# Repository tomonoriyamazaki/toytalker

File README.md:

# ToyTalker

子供向け音声AIおもちゃ。話しかけると、好きなキャラクターの声で返事をしてくれる。

## 特徴

- **応答約2秒**: STT→LLM→TTSを全区間ストリーミングでつなぎ、最初の音声チャンクが生成され次第再生を開始。サーバーレス（AWS Lambda）構成のまま体感レイテンシを最小化
- **相槌**: メインの応答を生成している間に「そうだね〜」などの短い繋ぎ応答を先に返し、会話のテンポを保つ
- **ボイス・キャラクター切替**: TTSプロバイダーをプラガブルに切替可能（OpenAI / Google / Gemini / ElevenLabs / Cartesia / FishAudio / ずんだもん / 自前クローンボイス）。キャラクターの人格プロンプトもDBで管理
- **スタンドアロン動作**: ESP32-S3搭載の専用基板、おもちゃ単体でWiFi経由でAWSと直接通信（設定ではスマホが必要）

## しくみ
https://github.com/user-attachments/assets/177e0598-6c0a-4d14-9477-36d719003d13

```
[スマホアプリ / ESP32] ── 音声 ──> Soniox STT（直接WebSocket接続）
        │                              │ テキスト
        │                              v
        │<── 音声ストリーム ── Lambda（LLM → TTS ストリーミング）
        │<── 繋ぎ応答 ─────── Lambda（相槌）
```

- STTはLambdaを経由せず、一時キーを使ってクライアントからSonioxへ直接接続（ボトルネック回避）
- LLM→TTSは直列ストリーミングで、生成しながら順次音声化・再生

## デバイスの変遷

| 世代 | 構成 | 状態 |
|---|---|---|
| v1 | Raspberry Pi | 検証完了 |
| v2 | ブレッドボード | 検証完了 |
| v3 | ESP32-S3スタンドアロン（専用PCB） | 開発中 |

## 参加プログラム

- SS Bootcamp 3rd #2025
- TiB FAB makers challenge 2025
- SS Bootcamp 4th #2026

## ドキュメント

- [開発のあゆみ（初期からの検討・試行錯誤の記録）](docs/history.md)
- [マイコン（ESP32）実装](docs/mcu.md)
- [スマホアプリ実装](app/README.md)
- [自前クローンボイス（RTX 5090 / Qwen3-TTS）のバッチ推論](docs/qwen3-tts-batch-engine-2026-09-12.md)
- [原価と課金の考え方](docs/pricing-and-cost-model.md)
- [製品化の認証チェックリスト（STマーク・技適・PSE）](docs/certification-checklist.md)

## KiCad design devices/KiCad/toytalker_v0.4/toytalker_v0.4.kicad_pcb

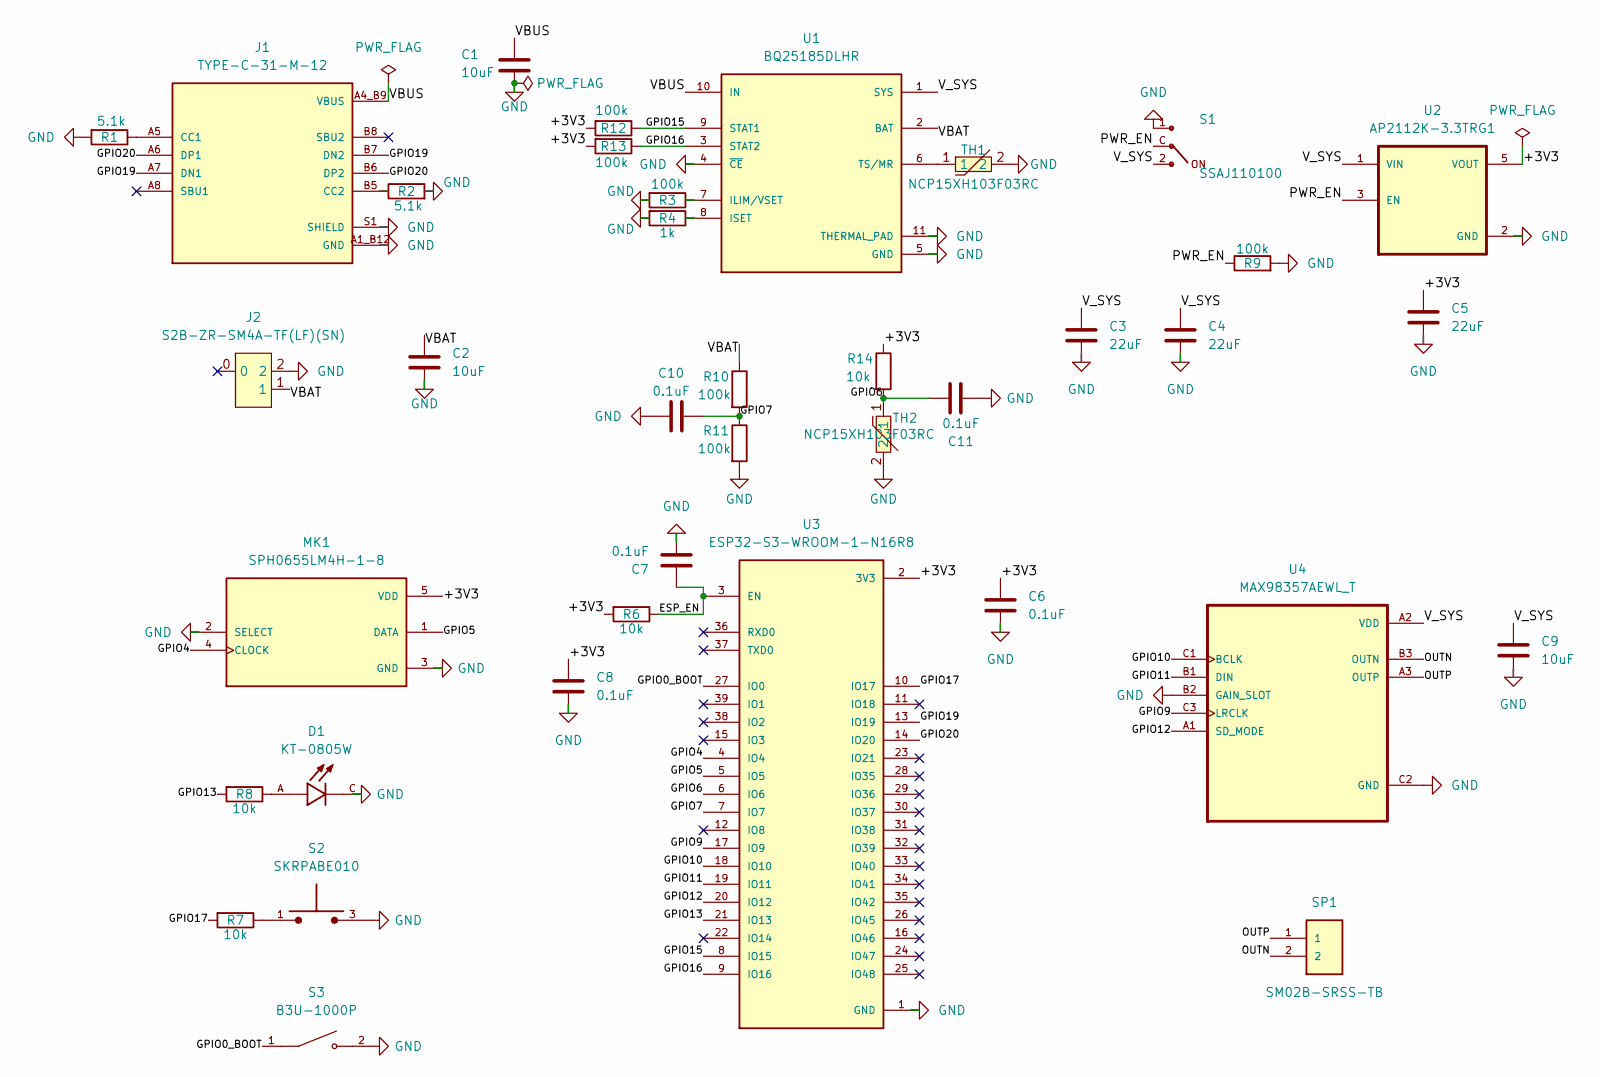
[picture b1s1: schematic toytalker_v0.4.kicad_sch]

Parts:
C1, C2, C9: 10uF; C_0603_1608Metric; LCSC Part C19702
C3, C4, C5: 22uF; C_0603_1608Metric; LCSC Part C59461
C6, C7, C8, C10, C11: 0.1uF; C_0402_1005Metric; LCSC Part C1525
D1: KT-0805W; LED_KT-0805W; PARTREV 2017.05.16; LCSC Part C34499
J1: TYPE-C-31-M-12; HRO_TYPE-C-31-M-12; PARTREV 2020.12.08; LCSC Part C165948
J2: S2B-ZR-SM4A-TF(LF)(SN); CONN-SMD_S2B-ZR-SM4A; LCSC Part C265329
MK1: SPH0655LM4H-1-8; MIC_SPH0655LM4H-1; LCSC Part C22376158
R1, R2: 5.1k; R_0402_1005Metric; LCSC Part C25905
R3, R9, R10, R11, R12, R13: 100k; R_0402_1005Metric; LCSC Part C25741
R4: 1k; R_0402_1005Metric; LCSC Part C11702
R6, R7, R8, R14: 10k; R_0402_1005Metric; LCSC Part C25744
S1: SSAJ110100; SW_SSAJ110100; LCSC Part C160863
S2: SKRPABE010; SW_SKRPABE010; LCSC Part C115360
S3: B3U-1000P; SW_B3U-1000P; LCSC Part C231329
SP1: SM02B-SRSS-TB; SM02B-SRSS-TB_LF__SN_; LCSC Part C160402
TH1, TH2: NCP15XH103F03RC; R0402; LCSC Part C77131
U1: BQ25185DLHR; IC_BQ25185DLHR; PARTREV OCTOBER 2023; LCSC Part C19725033
U2: AP2112K-3.3TRG1; SOT95P285X140-5N; PARTREV 2-2; LCSC Part C23380830
U3: ESP32-S3-WROOM-1-N16R8; XCVR_ESP32S3WROOM1N8R8; LCSC Part C2913202
U4: MAX98357AEWL_T; BGA9N40P3X3_134X143X69N; LCSC Part C2682619

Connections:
/+3V3: C5.1, C6.1, C8.1, MK1.5 (VDD), R6.2, R12.2, R13.2, R14.1, U2.5 (VOUT), U3.2 (3V3)
/ESP_EN: C7.1, R6.1, U3.3 (EN)
/GPIO0_BOOT: S3.1, U3.27 (IO0)
/GPIO4: MK1.4 (CLOCK), U3.4 (IO4)
/GPIO5: MK1.1 (DATA), U3.5 (IO5)
/GPIO6: C11.1, R14.2, TH2.1, U3.6 (IO6)
/GPIO7: C10.1, R10.2, R11.1, U3.7 (IO7)
/GPIO9: U3.17 (IO9), U4.C3 (LRCLK)
/GPIO10: U3.18 (IO10), U4.C1 (BCLK)
/GPIO11: U3.19 (IO11), U4.B1 (DIN)
/GPIO12: U3.20 (IO12), U4.A1 (SD_MODE)
/GPIO13: R8.2, U3.21 (IO13)
/GPIO15: R12.1, U1.9 (STAT1), U3.8 (IO15)
/GPIO16: R13.1, U1.3 (STAT2), U3.9 (IO16)
/GPIO17: R7.2, U3.10 (IO17)
/GPIO19: J1.A7 (DN1), J1.B7 (DN2), U3.13 (IO19)
/GPIO20: J1.A6 (DP1), J1.B6 (DP2), U3.14 (IO20)
/OUTN: SP1.2, U4.B3 (OUTN)
/OUTP: SP1.1, U4.A3 (OUTP)
/PWR_EN: R9.1, S1.C, U2.3 (EN)
/VBAT: C2.1, J2.1, R10.1, U1.2 (BAT)
/V_SYS: C3.1, C4.1, C9.1, S1.2, U1.1 (SYS), U2.1 (VIN), U4.A2 (VDD)
GND: C1.2, C2.2, C3.2, C4.2, C5.2, C6.2, C7.2, C8.2, C9.2, C10.2, C11.2, D1.C, J1.A1_B12 (GND), J1.B1_A12 (GND), J1.S1 (SHIELD), J1.S2 (SHIELD), J1.S3 (SHIELD), J1.S4 (SHIELD), J2.2, MK1.2 (SELECT), MK1.3 (GND), R1.2, R2.2, R3.2, R4.2, R9.2, R11.2, S1.1, S2.3, S2.4, S3.2, TH1.2, TH2.2, U1.4 (~CE), U1.5 (GND), U1.11 (THERMAL_PAD), U1.12 (THERMAL_PAD), U1.13 (THERMAL_PAD), U2.2 (GND), U3.1 (GND), U3.40 (GND), U3.41_1 (GND), U3.41_2 (GND), U3.41_3 (GND), U3.41_4 (GND), U3.41_5 (GND), U3.41_6 (GND), U3.41_7 (GND), U3.41_8 (GND), U3.41_9 (GND), U3.41_10 (GND), U3.41_11 (GND), U3.41_12 (GND), U3.41_13 (GND), U3.41_14 (GND), U3.41_15 (GND), U3.41_16 (GND), U3.41_17 (GND), U3.41_18 (GND), U3.41_19 (GND), U3.41_20 (GND), U3.41_21 (GND), U4.B2 (GAIN_SLOT), U4.C2 (GND)
unnamed: D1.A, R8.1
unnamed: J1.A5 (CC1), R1.1
unnamed: J1.B5 (CC2), R2.1
unnamed: R7.1, S2.1, S2.2
unnamed: R3.1, U1.7 (ILIM/VSET)
unnamed: R4.1, U1.8 (ISET)
unnamed: TH1.1, U1.6 (TS/MR)
VBUS: C1.1, J1.A4_B9 (VBUS), J1.B4_A9 (VBUS), U1.10 (IN)

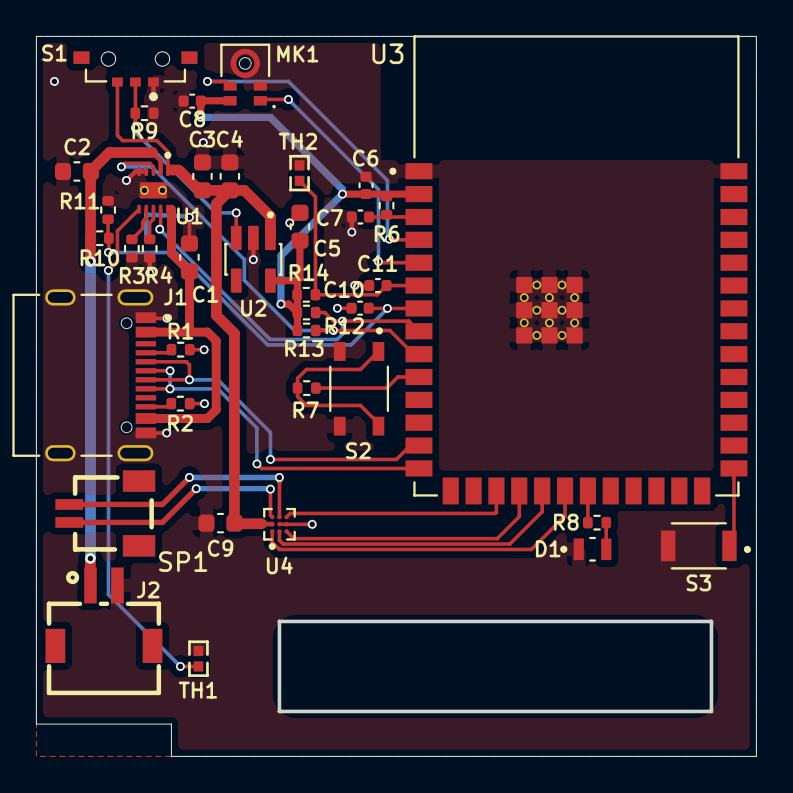
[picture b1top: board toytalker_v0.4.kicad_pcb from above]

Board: 2 copper layers, 40.0 x 40.0 mm, 38 parts (0 on the bottom side), 31 nets.

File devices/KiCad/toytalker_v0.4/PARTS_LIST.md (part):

# v0.4 パーツ一覧（ESP32-S3-WROOM-1-N16R8。2026-11-22）

> **このファイルの役割: 「今の正」。** 部品の値・ネット・役割の唯一の基準。BOM作成・発注チェック・値の確認はこのファイルだけを見る。変更したら必ずここを更新する。
> 変更の理由 → [マイコン](../../../docs/mcu.md) の「v0.4 で変えること」/ GPIO → [PINMAP.md](PINMAP.md) / v0.3 までの経緯 → [v0.3 の PARTS_LIST.md](../toytalker_mini_v0.3/PARTS_LIST.md) と [v0.2 の PARTS_AND_POWER.md](../toytalker_mini_v0.2/PARTS_AND_POWER.md)

検証方法: `toytalker_v0.4.kicad_sch` から全部品の値・フットプリント・`LCSC Part` を取り出し、ネットリスト（`kicad-cli sch export netlist`）で接続先を照合した。ERC 0件。部品は 38 個・20 種類。

## v0.3 からの変更点

| Ref | v0.3 | v0.4 | 理由・注意 |
|---|---|---|---|
| **U3** | ESP32-S3-MINI-1-N4R2 | **ESP32-S3-WROOM-1-N16R8**（C2913202） | フラッシュ 16MB・PSRAM 8MB（8 線）。18.0×25.5×3.1mm、縦置きでアンテナは基板の上辺。GPIO35〜37 は PSRAM が使うので配線しない。ビルドは `PSRAM=opi`・`FlashSize=16M`（MINI 機と同じ .bin は動かない） |
| **SP1** | HC-1.25-2PWT（MX1.25） | **SM02B-SRSS-TB**（JST SH 2P、C160402） | 小さくするため。差し口は基板の内側向き。1 = OUTP、2 = OUTN。固定用のパッド 3・4 はどこにもつながない |
| **R3** | 13kΩ（充電電圧 4.2V） | **100kΩ**（**4.1V**） | USB を挿したままでの電池の劣化を抑える。入力の上限は 1100mA のまま（BQ25185 データシート表 6-1）。使える容量は 1 割ほど減る見込み |
| **R4** | 620Ω（充電 484mA） | **1kΩ**（**300mA**） | 充電中の発熱と電池への負担を減らす（充電電流 = 300 / R）。充電時間は約 1.6 倍 |
| **R8** | 1.5kΩ | **10kΩ** | LED をさらに暗く（約 0.05〜0.07mA）。v0.3 の試験機で PWM 15% 相当に決めた |
| **R10・R11** | 470kΩ ×2 | **100kΩ ×2** | 電池の分圧。比は 1/2 のままで、計算式は変わらない。常時の電流は約 4.5 → 21µA |
| **C10・C11** | 0603 | **0402** | 0.1µF を 0402 に統一 |
| **U4** の GAIN | 未接続（9dB） | **GND**（12dB） | 隣の玉（C2 = GND）へ直結。効くかは実機で確認 |
| **U1** のシンボル | ピン 11 まで | **放熱ビア 12・13 を足した** | 基板の放熱ビア 2 個が「回路図から基板を更新」で GND から外れないように |
| ピン割当 | - | 全面的に変更 | [PINMAP.md](PINMAP.md)。アンプの BCLK と WS は配線の都合で入れ替えた（GPIO9 = WS、GPIO10 = BCLK） |

## パーツ一覧 ※電気の流れ順

### USB受電 → 充電IC
| Ref | 値 | ネット | 役割 |
|---|---|---|---|
| J1 | TYPE-C-31-M-12 | VBUS、GPIO19（D−）・GPIO20（D+） | USB-C。電源入力と USB-Serial/JTAG |
| R1 | 5.1kΩ | CC1 | USB-C「5V/3Aください」の名札(必須) |
| R2 | 5.1kΩ | CC2 | 同上(ケーブル裏表対応) |
| C1 | 10uF | VBUS | BQ25185のIN入力デカップリング |
| U1 | BQ25185 | - | 電源制御。充電しながら電力供給(パワーパス)。STAT1 → GPIO15、STAT2 → GPIO16 |
| R3 | **100kΩ** | ILIM/VSET | 🔁 充電電圧 4.1V・USB から最大 1.1A 受電の設定 |
| R4 | **1kΩ** | ISET | 🔁 バッテリーへ 300mA 充電の設定 |
| TH1 | NCP15XH103F03RC | TS/MR | 充電温度保護サーミスタ。高温/低温でBQが充電を自動停止。**電池コネクタの横に置く**（充電 IC のそばだと IC の熱を拾う） |

### バッテリー
| Ref | 値 | ネット | 役割 |
|---|---|---|---|
| J2 | S2B-ZR-SM4A-TF | VBAT | バッテリーコネクタ(JST ZH、φ1.0被覆線対応) |
| C2 | 10uF | VBAT | BQ25185のBAT側デカップリング |

### システム電源 V_SYS（常時通電）
| Ref | 値 | ネット | 役割 |
|---|---|---|---|
| C3 | 22uF | V_SYS | BQ25185のSYS出力デカップリング |
| C4 | 22uF | V_SYS | 同上追加分 |

### 電源スイッチ（EN方式 = 信号だけを切り替える）
| Ref | 値 | ネット | 役割 |
|---|---|---|---|
| S1 | SSAJ110100 | PWR_EN | スライドスイッチ（ALPS、横操作、SPDT）。C→PWR_EN、2→V_SYS、1→GND。C–2 が閉じると ON（大電流は流れない） |
| R9 | 100kΩ | PWR_EN | プルダウン。スイッチ切替中にENが宙ぶらりんになるのを防ぐ「重り」 |

### LDO → +3V3
| Ref | 値 | ネット | 役割 |
|---|---|---|---|
| U2 | AP2112K-3.3 | - | LDO。V_SYS→3.3Vに降圧。ENピンがPWR_ENで電源ON/OFF |
| C5 | 22uF | +3V3 | LDO出力デカップリング |
| C6 | 0.1uF | +3V3 | ESP32直近の高周波デカップリング（2 番ピンの横） |
| C8 | 0.1uF | +3V3 | マイク直近デカップリング（マイクの 3V3 のパッドの横。マイクを動かしたら一緒に動かす） |

### ESP32まわり
| Ref | 値 | ネット | 役割 |
|---|---|---|---|
| U3 | **ESP32-S3-WROOM-1-N16R8** | - | 🔁 本体（18.0×25.5mm、アンテナ部 6mm を含む） |
| R6 | 10kΩ | ESP_EN | ENプルアップ |
| C7 | 0.1uF | ESP_EN | ENの立ち上がり遅延+ノイズフィルタ |
| S3 | B3U-1000P | GPIO0_BOOT | Bootボタン |
| S2 | SKRPABE010 | GPIO17（R7 経由） | 機能ボタン(押すとGND) |
| R7 | 10kΩ | GPIO17 | ボタンとGPIOの間の直列抵抗(ピン保護) ※プルダウンではない |
| D1 | KT-0805W | GPIO13（R8 経由） | 単色LED（白、Vf 2.6〜3.0V @2mA、IF max 20mA） |
| R8 | **10kΩ** | GPIO13 | 🔁 LED電流制限（約 0.05〜0.07mA） |

### 監視・計測
| Ref | 値 | ネット | 役割 |
|---|---|---|---|
| R10 | **100kΩ** | VBAT→GPIO7 | 🔁 電池残量分圧の上側 |
| R11 | **100kΩ** | GPIO7→GND | 🔁 電池残量分圧の下側 |
| C10 | 0.1uF | GPIO7 | ADC安定化(WiFiノイズ平滑) |
| R12 | 100kΩ | GPIO15 | 充電状態STAT1プルアップ(STATはオープンドレインのため必須) |
| R13 | 100kΩ | GPIO16 | 充電状態STAT2プルアップ |
| R14 | 10kΩ | +3V3→GPIO6 | 基板温度分圧の上側 |
| TH2 | NCP15XH103F03RC | GPIO6→GND | 基板温度サーミスタ(分圧の下側) |
| C11 | 0.1uF | GPIO6 | ADC安定化 |

### 音声
| Ref | 値 | ネット | 役割 |
|---|---|---|---|
| MK1 | SPH0655LM4H-1-8 | GPIO4(CLOCK)/GPIO5(DATA) | **PDM** マイク。1=DATA→GPIO5、2=SELECT→GND、3=GND(リング)、4=CLOCK→GPIO4、5=VDD→+3V3。基板の上辺（電源スイッチの右隣）。音は基板の穴（Ø0.65）を通って裏側から入る |
| U4 | MAX98357A | - | I2Sアンプ。VDDは**V_SYS直結**。BCLK=GPIO10、LRCLK(WS)=GPIO9、DIN=GPIO11、SD=GPIO12、**GAIN=GND（12dB）** |
| C9 | 10uF | **V_SYS** | アンプVDDデカップリング ※+3V3ではない |
| SP1 | **SM02B-SRSS-TB** | OUTP/OUTN | 🔁 スピーカーコネクタ(JST SH) |

## プレフィックス順サマリ
- **J**: J1 USB-C / J2 バッテリー(ZH)
- **U**: U1 BQ25185 / U2 AP2112K / U3 ESP32-S3-WROOM-1-N16R8 / U4 MAX98357A
- **S**: S1 電源スライド(SSAJ110100) / S2 機能 / S3 Boot
- **R**: R1,R2=5.1k(CC) **R3=100k(ILIM/VSET)** **R4=1k(ISET)** R6=10k(EN) R7=10k(ボタン直列) **R8=10k(LED)** R9=100k(PWR_ENプルダウン) **R10,R11=100k(残量分圧)** R12,R13=100k(STATプルアップ) R14=10k(温度分圧)（R5 は欠番）
- **C**: C1,C2=10u(VBUS/VBAT) C3,C4=22u(V_SYS) C5=22u,C6=0.1u,C8=0.1u(+3V3) C7=0.1u(EN) C9=10u(V_SYS アンプ) C10,C11=0.1u(ADC)
- **TH**: TH1 充電保護 / TH2 基板温度 (同一品NCP15XH103F03RC)
- **他**: D1 LED / MK1 マイク(PDM) / SP1 スピーカー(SH)

## 発注用の一覧（LCSC 番号と Basic / Extended）

JLCPCB の部品データの写し（jlcsearch.tscircuit.com）で 2026-11-22 に引いた。**20 種類のうち Basic 8・Extended 12**（v0.3 は 23 種類のうち Extended 15）。在庫と Basic かどうかは発注前に注文画面で見直す。

| LCSC | 部品 | サイズ | Ref | 個数 | 区分 |
|---|---|---|---|---|---|
| C1525 | 0.1µF | 0402 | C6 C7 C8 C10 C11 | 5 | Basic |
| C19702 | 10µF | 0603 | C1 C2 C9 | 3 | Basic |
| C59461 | 22µF | 0603 | C3 C4 C5 | 3 | Basic |
| C25905 | 5.1kΩ | 0402 | R1 R2 | 2 | Basic |
| C11702 | 1kΩ | 0402 | R4 | 1 | Basic |
| C25744 | 10kΩ | 0402 | R6 R7 R8 R14 | 4 | Basic |
| C25741 | 100kΩ | 0402 | R3 R9 R10 R11 R12 R13 | 6 | Basic |
| C34499 | KT-0805W（白 LED） | 0805 | D1 | 1 | Basic |
| C77131 | NCP15XH103F03RC（サーミスタ 10kΩ） | 0402 | TH1 TH2 | 2 | Extended |
| C165948 | TYPE-C-31-M-12 | - | J1 | 1 | Extended |
| C265329 | S2B-ZR-SM4A-TF(LF)(SN) | - | J2 | 1 | Extended |
| C160402 | SM02B-SRSS-TB(LF)(SN) | - | SP1 | 1 | Extended |
| C22376158 | SPH0655LM4H-1-8 | - | MK1 | 1 | Extended |
| C160863 | SSAJ110100 | - | S1 | 1 | Extended |
| C115360 | SKRPABE010 | - | S2 | 1 | Extended |
| C231329 | B3U-1000P | - | S3 | 1 | Extended |
| C19725033 | BQ25185DLHR | - | U1 | 1 | Extended |
| C23380830 | AP2112K-3.3TRG1 | SOT-23-5 | U2 | 1 | Extended |
| C2913202 | ESP32-S3-WROOM-1-N16R8 | - | U3 | 1 | Extended |
| C2682619 | MAX98357AEWL+T | WLP-9 | U4 | 1 | Extended |

Extended のまま残した理由（LDO・サーミスタは Basic に合う品が無い）は [マイコン](../../../docs/mcu.md) の「v0.4 で変えること」14。

## JLCPCB の位置補正（Fabrication Toolkit 用）

`python devices/KiCad/tools/jlc_offset_check.py devices/KiCad/toytalker_v0.4/toytalker_v0.4.kicad_pcb` で照合した（2026-11-22）。値は回路図の部品の欄が正本で、基板のフットプリントへも写してある（道具の「今の値と違う」は 0 件）。

| Ref | FT Position Offset | FT Rotation Offset | メモ |
|---|---|---|---|
| J1 | 0,2.324 | - | v0.3 と同じ |
| MK1 | 0,0.706 | - | v0.3 と同じ |
| S1 | 0,0.603 | - | v0.3 と同じ |
| **SP1** | **0,0.038** | - | 新規。0.04mm なので実質ゼロ。向きは 0° で一致（固定用のパッド 3・4 の番号だけ JLC 側と左右が逆で、どちらも未接続なので問題ない） |
| **U3** | **0,-3.627** | - | 新規。JLC 側の原点はピンの並びの中心、うちはモジュール本体の中心で、その差。1〜40 番ピンで重ねて誤差 0.02mm |
| U1 | - | 270 | v0.3 と同じ |
| U2 | - | 180 | v0.3 と同じ |
| U4 | - | 180 | v0.3 と同じ |

D1（LED）はパッドの名前が JLC 側と違い（A/C と 1/2）、道具では向きを決められない。v0.3 と同じ部品・同じフットプリントで、v0.3 の注文で向きが合っていた。

## パッケージサイズの使い分け

サイズ表記: **0402** = 1.0×0.5mm / **0603** = 1.6×0.8mm（インチ由来の呼び名。メートル表記だと1005/1608でKiCadのフットプリント名はこちら）

| 種類 | サイズ | 理由 |
|---|---|---|
| 抵抗 全部(R1〜R14, TH1/TH2) | **0402** | 抵抗のサイズは**発熱**で決まり、値は無関係 |
| コンデンサ 0.1µF (C6/C7/C8/C10/C11) | **0402** | 小容量は小さい体積で作れる |
| コンデンサ 10〜22µF (C1〜C5, C9) | **0603** | 容量は物理体積が必要。0402の10µFは高価な上、電圧がかかると実効容量が大きく落ちる(DCバイアス特性)ため0603が定石 |

## 設計の状態（2026-11-22）

- **未発注（製造ファイルまで済み）。** 回路図・配置・配線・スピーカーの裏のくり抜き・アンテナのキープアウトまで済み。経過と残りは [マイコン](../../../docs/mcu.md) の「v0.4 の状態」。
- **ERC**: 0件。**DRC**（ゾーン再充填後、回路図との照合つき）: 未配線 0、間隔の違反なし。残る指摘は既知のもの（U4 BGA のマスク橋渡し 12、J1 シールドの基板端 0.48mm 2、U3・J1 の外形線が基板端にかかる 5、シルクの重なり、U3 の 40 番ピンのベタとのつながりが細い 1）。
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
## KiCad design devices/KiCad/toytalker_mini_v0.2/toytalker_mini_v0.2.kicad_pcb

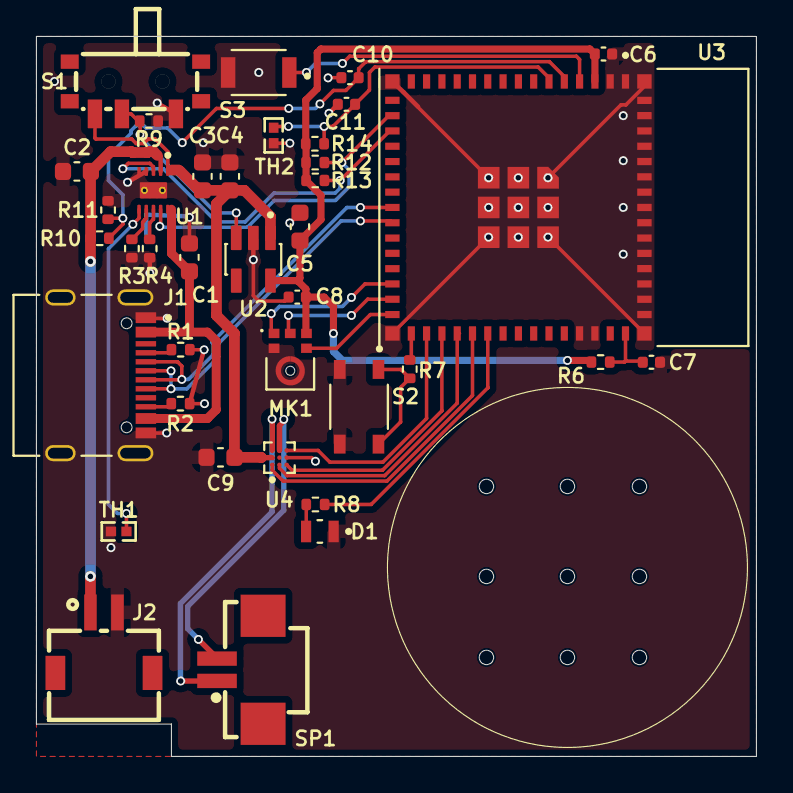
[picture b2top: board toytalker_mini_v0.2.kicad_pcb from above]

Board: 2 copper layers, 40.0 x 40.0 mm, 38 parts (0 on the bottom side), 32 nets.

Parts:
C1, C2, C9: 10uF; C_0603_1608Metric
C3, C4, C5: 22uF; C_0603_1608Metric
C6, C7, C8, C10, C11: 0.1uF; C_0402_1005Metric
D1: KT-0805W; LED_KT-0805W
J1: TYPE-C-31-M-12; HRO_TYPE-C-31-M-12
J2: S2B-ZR-SM4A-TF(LF)(SN); CONN-SMD_S2B-ZR-SM4A
MK1: SPH0645LM4H-1-8; MIC_SPH0645LM4H-B
R1, R2: 5.1k; R_0402_1005Metric
R3: 13k; R_0402_1005Metric
R4: 620; R_0402_1005Metric
R6, R7, R14: 10k; R_0402_1005Metric
R8: 470; R_0402_1005Metric
R9, R12, R13: 100k; R_0402_1005Metric
R10, R11: 470k; R_0402_1005Metric
S1: MSK12C02G15-B; SW-SMD_MSK12C02G15-B
S2: SKRPABE010; SW_SKRPABE010
S3: B3U-1000P; SW_B3U-1000P
SP1: HC-1.25-2PWT; CONN-SMD_2P-P1.25-HC-1.25-2PWT
TH1, TH2: NCP15XH103F03RC; R0402
U1: BQ25185DLHR; IC_BQ25185DLHR
U2: AP2112K-3.3TRG1; SOT95P285X140-5N
U3: ESP32-S3-MINI-1-N4R2; XCVR_ESP32-S3-MINI-1-N4R2
U4: MAX98357AEWL_T; BGA9N40P3X3_134X143X69N

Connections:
/+3V3: C5.1, C6.1, C8.1, MK1.5 (VDD), R6.2, R12.2, R13.2, R14.1, U2.5 (VOUT), U3.3 (3V3)
/ESP_EN: C7.1, R6.1, U3.45 (EN)
/GPIO0_BOOT: S3.1, U3.4 (IO0)
/GPIO1: C10.1, R10.2, R11.1, U3.5 (IO1)
/GPIO2: C11.1, R14.2, TH2.1, U3.6 (IO2)
/GPIO13: R12.1, U1.9 (STAT1), U3.17 (IO13)
/GPIO14: R13.1, U1.3 (STAT2), U3.18 (IO14)
/GPIO19: J1.A7 (DN1), J1.B7 (DN2), U3.23 (IO19)
/GPIO20: J1.A6 (DP1), J1.B6 (DP2), U3.24 (IO20)
/GPIO33: MK1.1 (WS), U3.28 (IO33)
/GPIO34: MK1.6 (DATA_OUT), U3.29 (IO34)
/GPIO35: R7.2, U3.31 (IO35)
/GPIO36: U3.32 (IO36), U4.C3 (LRCLK)
/GPIO37: U3.33 (IO37), U4.C1 (BCLK)
/GPIO38: U3.34 (IO38), U4.B1 (DIN)
/GPIO39: U3.35 (IO39), U4.A1 (SD_MODE)
/GPIO40: R8.2, U3.36 (IO40)
/GPIO48: MK1.4 (BCLK), U3.30 (IO48)
/OUTN: SP1.2, U4.B3 (OUTN)
/OUTP: SP1.1, U4.A3 (OUTP)
/PWR_EN: R9.1, S1.2, U2.3 (EN)
/VBAT: C2.1, J2.1, R10.1, U1.2 (BAT)
/V_SYS: C3.1, C4.1, C9.1, S1.1, U1.1 (SYS), U2.1 (VIN), U4.A2 (VDD)
GND: C1.2, C2.2, C3.2, C4.2, C5.2, C6.2, C7.2, C8.2, C9.2, C10.2, C11.2, D1.C, J1.A1_B12 (GND), J1.B1_A12 (GND), J1.S1 (SHIELD), J1.S2 (SHIELD), J1.S3 (SHIELD), J1.S4 (SHIELD), J2.2, MK1.2 (SELECT), MK1.3 (GND), R1.2, R2.2, R3.2, R4.2, R9.2, R11.2, S1.3, S2.3, S2.4, S3.2, TH1.2, TH2.2, U1.4 (~CE), U1.5 (GND), U1.11 (THERMAL_PAD), U1.12, U1.13, U2.2 (GND), U3.1 (GND), U3.2 (GND), U3.42 (GND), U3.43 (GND), U3.46 (GND), U3.47 (GND), U3.48 (GND), U3.49 (GND), U3.50 (GND), U3.51 (GND), U3.52 (GND), U3.53 (GND), U3.54 (GND), U3.55 (GND), U3.56 (GND), U3.57 (GND), U3.58 (GND), U3.59 (GND), U3.60 (GND), U3.61 (GND), U3.61_1 (GND), U3.61_2 (GND), U3.61_3 (GND), U3.61_4 (GND), U3.61_5 (GND), U3.61_6 (GND), U3.61_7 (GND), U3.61_8 (GND), U3.62 (GND), U3.63 (GND), U3.64 (GND), U3.65 (GND), U4.C2 (GND)
unnamed: D1.A, R8.1
unnamed: J1.A5 (CC1), R1.1
unnamed: J1.B5 (CC2), R2.1
unnamed: R7.1, S2.1, S2.2
unnamed: R3.1, U1.7 (ILIM/VSET)
unnamed: R4.1, U1.8 (ISET)
unnamed: TH1.1, U1.6 (TS/MR)
VBUS: C1.1, J1.A4_B9 (VBUS), J1.B4_A9 (VBUS), U1.10 (IN)

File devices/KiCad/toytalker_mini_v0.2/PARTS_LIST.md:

# v0.2 パーツ一覧（回路図から機械抽出した実値・2026-08-29検証）

> **このファイルの役割: 「今の正」。** 部品の値・ネット・役割の唯一の基準。BOM作成・発注チェック・値の確認はこのファイルだけを見る。変更したら必ずここを更新する。
> 経緯・理由 → PARTS_AND_POWER.md / 作業ログ → SCHEMATIC_CHECKLIST.md / GPIO → PINMAP.md

検証方法: `toytalker_mini_v0.2.kicad_sch` から全Reference/Valueを抽出し、ネットリストで接続先を照合。

## パーツ一覧 ※電気の流れ順

### USB受電 → 充電IC
| Ref | 値 | ネット | 役割 |
|---|---|---|---|
| J1 | TYPE-C-31-M-12 | VBUS | USB-C電源入力 |
| R1 | 5.1kΩ | CC1 | USB-C「5V/3Aください」の名札(必須) |
| R2 | 5.1kΩ | CC2 | 同上(ケーブル裏表対応) |
| C1 | 10uF | VBUS | BQ25185のIN入力デカップリング |
| U1 | BQ25185 | - | 電源制御。充電しながら電力供給(パワーパス) |
| R3 | 13kΩ | ILIM/VSET | USBから最大1.1A受電の設定 |
| R4 | **620Ω** | ISET | バッテリーへ500mA充電の設定 |
| TH1 | NCP15XH103F03RC | TS/MR | 🆕 充電温度保護サーミスタ。高温/低温でBQが充電を自動停止(旧R5の置き換え) |

### バッテリー
| Ref | 値 | ネット | 役割 |
|---|---|---|---|
| J2 | S2B-ZR-SM4A-TF | VBAT | 🆕 バッテリーコネクタ(JST ZH。旧SHから変更、φ1.0被覆線対応) |
| C2 | 10uF | VBAT | BQ25185のBAT側デカップリング |

### システム電源 V_SYS（常時通電）
| Ref | 値 | ネット | 役割 |
|---|---|---|---|
| C3 | 22uF | V_SYS | BQ25185のSYS出力デカップリング |
| C4 | 22uF | V_SYS | 同上追加分 ※旧V_SYS_SW用→v0.2でV_SYS_SW系統は廃止 |

### 電源スイッチ（EN方式 = 信号だけを切り替える）
| Ref | 値 | ネット | 役割 |
|---|---|---|---|
| S1 | MSK12C02G15-B | PWR_EN | 🆕 スライドスイッチ。V_SYS/GNDを選んでPWR_ENへ(大電流は流れない) |
| R9 | 100kΩ | PWR_EN | プルダウン。スイッチ切替中にENが宙ぶらりんになるのを防ぐ「重り」 |

### LDO → +3V3
| Ref | 値 | ネット | 役割 |
|---|---|---|---|
| U2 | AP2112K-3.3 | - | LDO。V_SYS→3.3Vに降圧。ENピンがPWR_ENで電源ON/OFF |
| C5 | 22uF | +3V3 | LDO出力デカップリング |
| C6 | 0.1uF | +3V3 | ESP32直近の高周波デカップリング |
| C8 | 0.1uF | +3V3 | マイク直近デカップリング |

### ESP32まわり
| Ref | 値 | ネット | 役割 |
|---|---|---|---|
| U3 | ESP32-S3-MINI-1-N4R2 | - | 本体（実寸15.4×20.5mm、アンテナ部5.05mm含む） |
| R6 | 10kΩ | ESP_EN | ENプルアップ |
| C7 | 0.1uF | ESP_EN | ENの立ち上がり遅延+ノイズフィルタ |
| S3 | B3U-1000P | GPIO0_BOOT | Bootボタン |
| S2 | SKRPABE010 | (GPIO7) | 機能ボタン(押すとGND) |
| R7 | 10kΩ | GPIO7 | ボタンとGPIOの間の直列抵抗(ピン保護) ※プルダウンではない |
| D1 | KT-0805W | (GPIO8) | 単色LED |
| R8 | **470Ω** | GPIO8 | LED電流制限。v0.2で47Ω→470Ωに変更(減光、約2.8mA) |

### 監視・計測（v0.2新設）
| Ref | 値 | ネット | 役割 |
|---|---|---|---|
| R10 | 470kΩ | VBAT→GPIO1 | 🆕 電池残量分圧の上側 |
| R11 | 470kΩ | GPIO1→GND | 🆕 電池残量分圧の下側 |
| C10 | **0.1uF** | GPIO1 | 🆕 ADC安定化(WiFiノイズ平滑) |
| R12 | 100kΩ | GPIO13 | 🆕 充電状態STAT1プルアップ(STATはオープンドレインのため必須) |
| R13 | 100kΩ | GPIO14 | 🆕 充電状態STAT2プルアップ |
| R14 | 10kΩ | +3V3→GPIO2 | 🆕 基板温度分圧の上側 |
| TH2 | NCP15XH103F03RC | GPIO2→GND | 🆕 基板温度サーミスタ(分圧の下側) |
| C11 | 0.1uF | GPIO2 | 🆕 ADC安定化 |

### 音声
| Ref | 値 | ネット | 役割 |
|---|---|---|---|
| MK1 | SPH0645LM4H | GPIO4/5/9 | I2Sマイク |
| U4 | MAX98357A | - | I2Sアンプ。VDDは**V_SYS直結**(v0.2変更。3.3Vでは音量パワー不足のため) |
| C9 | 10uF | **V_SYS** | アンプVDDデカップリング ※+3V3ではない |
| SP1 | HC-1.25-2PWT | OUTP/OUTN | 🆕 スピーカーコネクタ(MX1.25互換。旧SHから変更) |

## v0.1からの削除
- R5 (10kΩ TS/MR固定抵抗) → TH1に置き換え
- 旧J2/旧SP1 (JST SH) → ZH / MX1.25に変更
- 旧S1 (SSAJ110100) → MSK12C02G15-Bに変更
- V_SYS_SWネット → EN方式化により廃止

## プレフィックス順サマリ
- **J**: J1 USB-C / J2 バッテリー(ZH)
- **U**: U1 BQ25185 / U2 AP2112K / U3 ESP32-S3-MINI-1 / U4 MAX98357A
- **S**: S1 電源スライド / S2 機能 / S3 Boot
- **R**: R1,R2=5.1k(CC) R3=13k(ILIM) R4=620(ISET) R6=10k(EN) R7=10k(ボタン直列) R8=470(LED) R9=100k(PWR_ENプルダウン) R10,R11=470k(残量分圧) R12,R13=100k(STATプルアップ) R14=10k(温度分圧)
- **C**: C1,C2=10u(VBUS/VBAT) C3,C4=22u(V_SYS) C5=22u,C6=0.1u,C8=0.1u(+3V3) C7=0.1u(EN) C9=10u(V_SYS アンプ) C10,C11=0.1u(ADC)
- **TH**: TH1 充電保護 / TH2 基板温度 (同一品NCP15XH103F03RC)
- **他**: D1 LED / MK1 マイク / SP1 スピーカー
